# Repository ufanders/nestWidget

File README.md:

# nestWidget
Here lies a device to bridge the gap between a Nest learning thermostat and my in-wall, electric forced-air room heater.

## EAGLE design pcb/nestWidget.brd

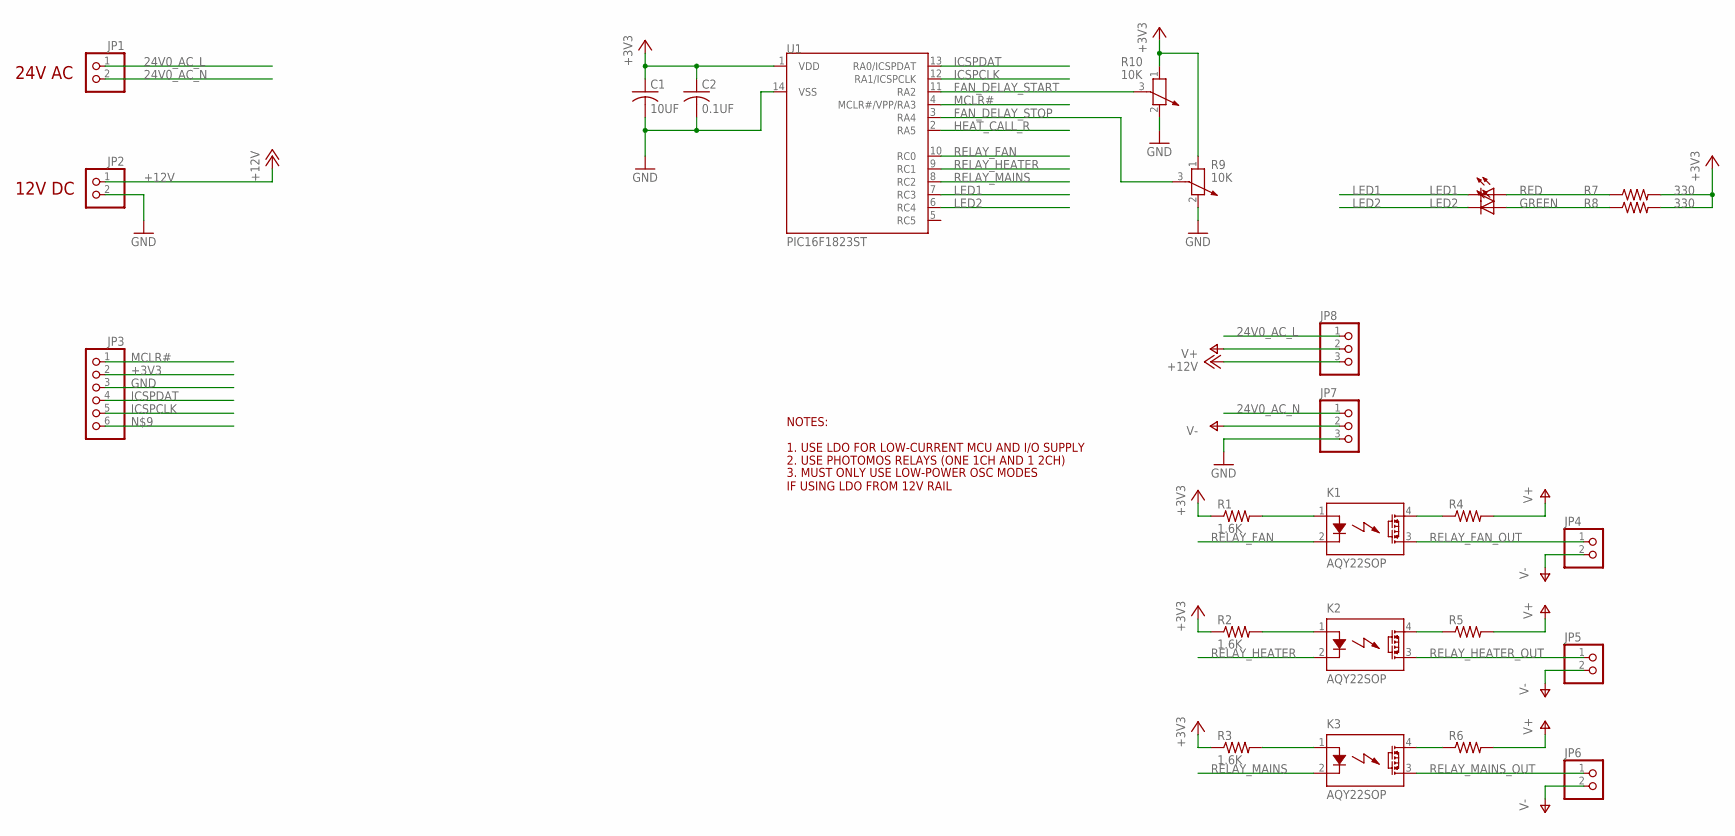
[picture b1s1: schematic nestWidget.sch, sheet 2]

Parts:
C1: 10UF; C0603
C2: 0.1UF; C0603
JP1, JP2, JP4, JP5, JP6: PINHD-1X2; 1X02
JP3: PINHD-1X6; 1X06
JP7, JP8: PINHD-1X3; 1X03
K1, K2, K3: AQY22SOP; SOP04
LED1: RED; CHIPLED_0603
LED2: GREEN; CHIPLED_0603
R1, R2, R3: 1.6K; R0603
R4, R5, R6: R-US_R0603; R0603
R7, R8: 330; R0603
R9, R10: 10K; PT-10S
U1: PIC16F1823ST; TSSOP14

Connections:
24V0_AC_L: JP1.1, JP8.1
24V0_AC_N: JP1.2, JP7.1
+3V3: C1.1, C2.1, JP3.2, R1.1, R2.1, R3.1, R7.2, R8.2, R9.1, R10.1, U1.1 (VDD)
+12V: JP2.1, JP8.3
FAN_DELAY_START: R10.3, U1.11 (RA2)
FAN_DELAY_STOP: R9.3, U1.3 (RA4)
GND: C1.2, C2.2, JP2.2, JP3.3, JP7.3, R9.2, R10.2, U1.14 (VSS)
HEAT_CALL_R: U1.2 (RA5)
ICSPCLK: JP3.5, U1.12 (RA1/ICSPCLK)
ICSPDAT: JP3.4, U1.13 (RA0/ICSPDAT)
LED1: LED1.C, U1.7 (RC3)
LED2: LED2.C, U1.6 (RC4)
MCLR#: JP3.1, U1.4 (MCLR#/VPP/RA3)
unnamed: K1.1 (A), R1.2
unnamed: K2.1 (A), R2.2
unnamed: K3.1 (A), R3.2
unnamed: K3.4 (DS1), R6.1
unnamed: K2.4 (DS1), R5.1
unnamed: K1.4 (DS1), R4.1
unnamed: LED1.A, R7.1
unnamed: LED2.A, R8.1
RELAY_FAN: K1.2 (K), U1.10 (RC0)
RELAY_FAN_OUT: JP4.1, K1.3 (DS2)
RELAY_HEATER: K2.2 (K), U1.9 (RC1)
RELAY_HEATER_OUT: JP5.1, K2.3 (DS2)
RELAY_MAINS: K3.2 (K), U1.8 (RC2)
RELAY_MAINS_OUT: JP6.1, K3.3 (DS2)
V+: JP8.2, R4.2, R5.2, R6.2
V-: JP4.2, JP5.2, JP6.2, JP7.2

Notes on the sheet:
24V AC
12V DC
NOTES:
1. USE LDO FOR LOW-CURRENT MCU AND I/O SUPPLY
2. USE PHOTOMOS RELAYS (ONE 1CH AND 1 2CH)
3. MUST ONLY USE LOW-POWER OSC MODES IF USING LDO FROM 12V RAIL

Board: 2 copper layers, 26 parts (0 on the bottom side), 28 nets, no tracks yet.

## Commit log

2015-11-18 First commit.
2015-11-24 Added most parts.
2016-01-09 First commit. -Most things there.
